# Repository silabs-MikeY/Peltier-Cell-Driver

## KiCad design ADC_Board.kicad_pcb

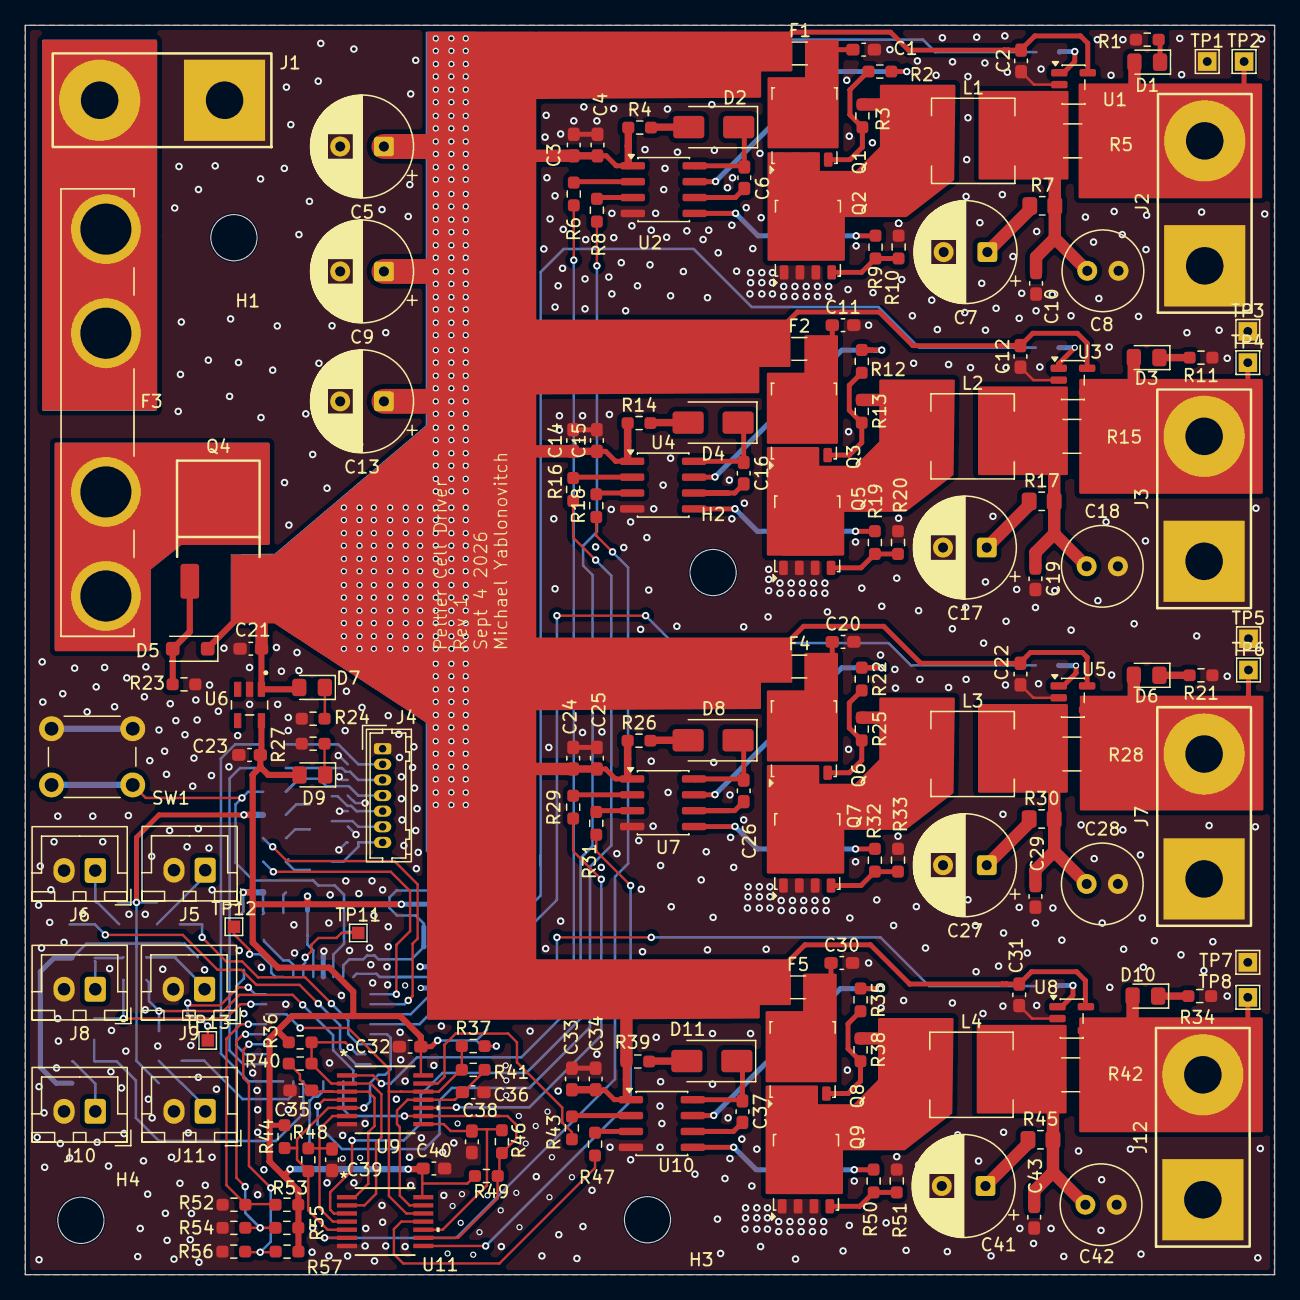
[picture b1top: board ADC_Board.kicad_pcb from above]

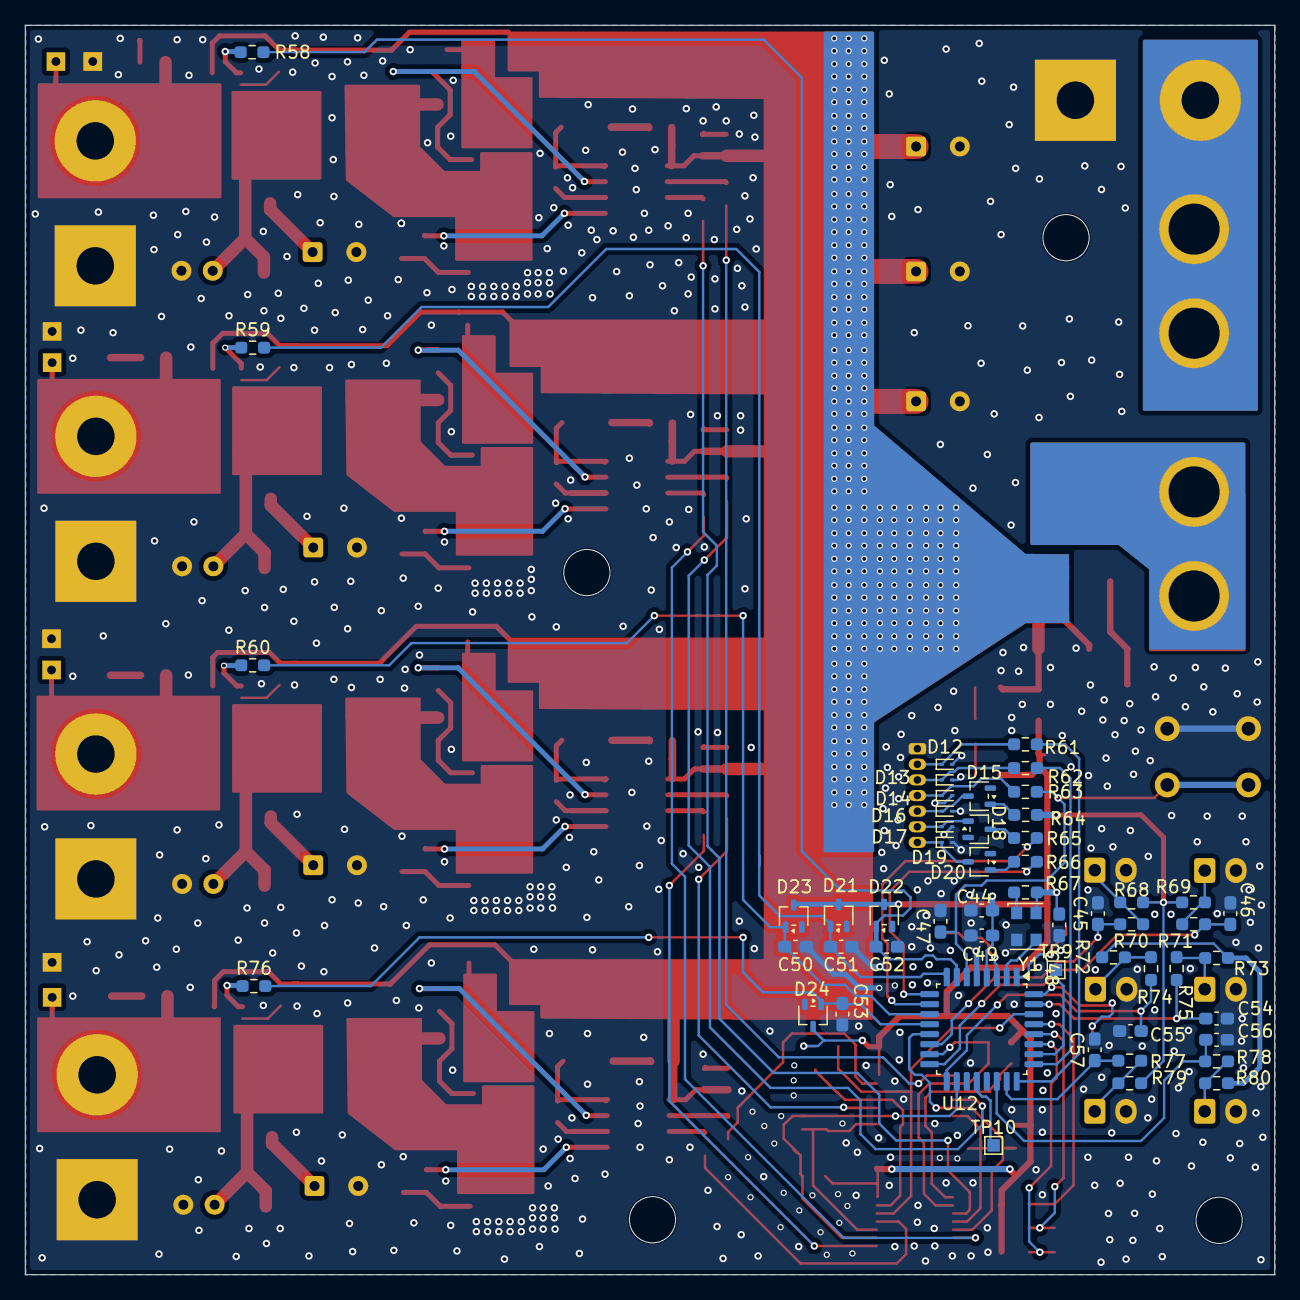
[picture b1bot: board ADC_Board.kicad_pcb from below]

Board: 4 copper layers, 100.0 x 100.0 mm, 222 parts (54 on the bottom side), 128 nets.

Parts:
C1, C11, C20, C21, C30, C45, C46, C54, C55, C56, C57: 1u; C_0603_1608Metric_Pad1.08x0.95mm_HandSolder
C2, C4, C6, C12, C15, C16, C22, C25, C26, C31, C32, C34, C37, C40, C47, C48, C49, C50, C51, C52, C53: 100n; C_0603_1608Metric_Pad1.08x0.95mm_HandSolder
C3, C14, C24, C33, C44: 4u7; C_0603_1608Metric_Pad1.08x0.95mm_HandSolder
C5, C7, C9, C13, C17, C27, C41: 100u; CP_Radial_D8.0mm_P3.50mm
C8, C18, C28, C42: 22u; C_Radial_D6.3mm_H7.0mm_P2.50mm
C10, C19, C29, C43: DNP; C_0603_1608Metric_Pad1.08x0.95mm_HandSolder
C23: 2u2; C_0603_1608Metric_Pad1.08x0.95mm_HandSolder
C35, C36, C38, C39: 330p; C_0603_1608Metric_Pad1.08x0.95mm_HandSolder
D1, D3, D6, D7, D9, D10: LED; LED_0805_2012Metric_Pad1.15x1.40mm_HandSolder
D2, D4, D8, D11: SS14; D_SMA
D5: BZT52C10; D_SOD-123F
D12, D13, D14, D16, D17, D19: ESD9B3.3ST5G; D_SOD-923
D15, D18, D20, D21, D22, D23, D24: BAT54W; SOT-323_SC-70
F1, F2, F4, F5: 5A; Fuse_1206_3216Metric
F3: 3555-2; FUSE_3555-2
H1, H2, H3, H4: MountingHole; MountingHole_3.7mm
J1, J2, J3, J7, J12: Wire_Solder_2Pin; Wire_Solder_2Pin_12-14AWG_P10mm_D3.0mm
J4: Conn_01x07_Socket; Hirose_DF13-07P-1.25DSA_1x07_P1.25mm_Vertical
J5, J6, J8, J9, J10, J11: Conn_01x02_Pin; JST_XH_B2B-XH-A_1x02_P2.50mm_Vertical
L1, L2, L3, L4: 1u; L_Changjiang_FXL0630
Q1, Q2, Q3, Q5, Q6, Q7, Q8, Q9: NVMFS5C468NL-HXY
Q4: DOD40P03; DOD40P03_TO-252_Q_PMOS_DGS
R1, R3, R10, R11, R13, R20, R21, R23, R24, R25, R27, R33, R34, R36, R37, R38, R44, R49, R51, R68, R69, R72, R73, R79, R80: 10k; R_0603_1608Metric_Pad0.98x0.95mm_HandSolder
R2, R9, R12, R19, R22, R32, R35, R50: 4r7; R_0603_1608Metric_Pad0.98x0.95mm_HandSolder
R4, R14, R26, R39: 10r; R_0603_1608Metric_Pad0.98x0.95mm_HandSolder
R5, R15, R28, R42: 5m; R_1210_3225Metric_Pad1.30x2.65mm_HandSolder
R6, R8, R16, R18, R29, R31, R43, R47, R61, R62, R63, R64, R65, R66: 100r; R_0603_1608Metric_Pad0.98x0.95mm_HandSolder
R7, R17, R30, R45: 500m; R_0805_2012Metric_Pad1.20x1.40mm_HandSolder
R40, R41, R46, R48, R58, R59, R60, R67, R70, R71, R74, R75, R76, R77, R78: 1k; R_0603_1608Metric_Pad0.98x0.95mm_HandSolder
R52, R53, R54, R55, R56, R57: DNP; R_0603_1608Metric_Pad0.98x0.95mm_HandSolder
SW1: SW_Push; SW_PUSH_6mm
TP1, TP3, TP5, TP7: GND; TestPoint_THTPad_1.5x1.5mm_Drill0.7mm
TP2, TP4, TP6, TP8: TestPoint; TestPoint_THTPad_1.5x1.5mm_Drill0.7mm
TP9, TP10, TP11, TP12, TP13: TestPoint; TestPoint_Pad_1.0x1.0mm
U1, U3, U5, U8: INA281A3; SOT-23-5
U2, U4, U7, U10: LM5109BMA; SOIC-8_3.9x4.9mm_P1.27mm
U6: TPS70933DBVR; SOT95P280X145-5N
U9: SN74HCS02PWR; TSSOP14_PW_TEX-M
U11: SN74HCS08PWR; TSSOP14_PW_TEX-M
U12: STM32G030K6Tx; LQFP-32_7x7mm_P0.8mm
Y1: HSO321S 16MHZ 3.3V; Oscillator_SMD_EuroQuartz_XO32-4Pin_3.2x2.5mm

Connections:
+3.3V: C23.1, C32.1, C40.1, C44.1, C48.2, C49.1, D9.2 (A), D21.3 (K), D22.3 (K), D23.3 (K), D24.3 (K), R36.2, R37.2, R44.2, R49.2, R53.2, R55.2, R57.2, R64.1, R67.2, R68.2, R69.2, R72.2, R73.2, R79.2, R80.2, U6.5 (OUT), U9.14 (VCC), U11.14 (VCC), U12.4 (VDD), Y1.4 (VDD)
+12V: C2.2, C3.1, C4.1, C5.1, C9.1, C12.2, C13.1, C14.1, C15.1, C21.1, C22.2, C24.1, C25.1, C31.2, C33.1, C34.1, D5.1 (K), D7.2 (A), F1.1, F2.1, F4.1, F5.1, Q4.3 (S), R4.1, R14.1, R26.1, R39.1, U1.5 (V+), U2.1 (VDD), U3.5 (V+), U4.1 (VDD), U5.5 (V+), U6.1 (IN), U7.1 (VDD), U8.5 (V+), U10.1 (VDD)
/PWM Driver/PWM3_DLY: C38.1, R46.2, U9.8 (3A), U11.10 (3B)
/PWM Driver/PWM4_DLY: C36.1, R41.2, U9.11 (4A), U11.13 (4B)
/PWM Driver/PWM_1_DLY: C35.1, R40.2, U9.3 (1B), U11.1 (1A)
/PWM Driver/PWM_2_DLY: C39.1, R48.2, U9.6 (2B), U11.4 (2A)
/Root/ADDR_0: R56.2, R57.1, U12.27 (PB3)
/Root/ADDR_1: R54.2, R55.1, U12.28 (PB4)
/Root/ADDR_2: R52.2, R53.1, U12.29 (PB5)
ADC_MOTOR_CURRENT_1: C52.2, D22.1 (A), R58.2, U12.7 (PA0)
ADC_MOTOR_CURRENT_2: C51.2, D21.1 (A), R59.2, U12.8 (PA1)
ADC_MOTOR_CURRENT_3: C50.2, D23.1 (A), R60.2, U12.11 (PA4)
ADC_MOTOR_CURRENT_4: C53.2, D24.1 (A), R76.2, U12.12 (PA5)
ADC_THERMISTOR_1: C45.1, R70.2, U12.14 (PA7)
ADC_THERMISTOR_2: C46.1, R71.2, U12.16 (PB1)
ADC_THERMISTOR_3: C55.1, R74.2, U12.17 (PB2)
ADC_THERMISTOR_4: C54.1, R75.2, U12.31 (PB7)
ADC_THERMISTOR_5: C56.1, R78.2, U12.22 (PA9/PA11)
ADC_THERMISTOR_6: C57.1, R77.2, U12.23 (PA10/PA12)
GND: C1.2, C2.1, C3.2, C4.2, C5.2, C7.2, C8.2, C9.2, C10.2, C11.2, C12.1, C13.2, C14.2, C15.2, C17.2, C18.2, C19.2, C20.2, C21.2, C22.1, C23.2, C24.2, C25.2, C27.2, C28.2, C29.2, C30.2, C31.1, C32.2, C33.2, C34.2, C35.2, C36.2, C38.2, C39.2, C40.2, C41.2, C42.2, C43.2, C44.2, C45.2, C46.2, C47.2, C48.1, C49.2, C50.1, C51.1, C52.1, C53.1, C54.2, C55.2, C56.2, C57.2, D12.2 (A2), D13.2 (A2), D14.2 (A2), D16.2 (A2), D17.2 (A2), D19.2 (A2), J1.1 (WIRE1), J2.1 (WIRE1), J3.1 (WIRE1), J4.1, J5.2, J6.2, J7.1 (WIRE1), J8.2, J9.2, J10.2, J11.2, J12.1 (WIRE1), Q2.3 (S), Q5.3 (S), Q7.3 (S), Q9.3 (S), R1.1, R10.1, R11.1, R20.1, R21.1, R23.1, R24.1, R27.1, R33.1, R34.1, R51.1, R52.1, R54.1, R56.1, SW1.2, TP1.1 (1_1), TP3.1 (1_1), TP5.1 (1_1), TP7.1 (1_1), U1.2 (GND), U2.4 (VSS), U3.2 (GND), U4.4 (VSS), U5.2 (GND), U6.2 (GND), U7.4 (VSS), U8.2 (GND), U9.7 (GND), U10.4 (VSS), U11.7 (GND), U12.5 (VSS), Y1.2 (GND)
unnamed: C7.1, R7.1
unnamed: C17.1, R17.1
unnamed: C27.1, R30.1
unnamed: C41.1, R45.1
unnamed: D1.2 (A), J2.2 (WIRE2), R5.2, TP2.1 (1_1), U1.4 (Vin-)
unnamed: D1.1 (K), R1.2
unnamed: D2.2 (A), R4.2
unnamed: C6.1, D2.1 (K), U2.8 (HB)
unnamed: D3.2 (A), J3.2 (WIRE2), R15.2, TP4.1 (1_1), U3.4 (Vin-)
unnamed: D3.1 (K), R11.2
unnamed: D4.2 (A), R14.2
unnamed: C16.1, D4.1 (K), U4.8 (HB)
unnamed: D5.2 (A), Q4.2 (G), R23.2
unnamed: D6.2 (A), J7.2 (WIRE2), R28.2, TP6.1 (1_1), U5.4 (Vin-)
unnamed: D6.1 (K), R21.2
unnamed: D7.1 (K), R24.2
unnamed: D8.2 (A), R26.2
unnamed: C26.1, D8.1 (K), U7.8 (HB)
unnamed: D9.1 (K), R27.2
unnamed: D10.2 (A), J12.2 (WIRE2), R42.2, TP8.1 (1_1), U8.4 (Vin-)
unnamed: D10.1 (K), R34.2
unnamed: D11.2 (A), R39.2
unnamed: C37.1, D11.1 (K), U10.8 (HB)
unnamed: D12.1 (A1), J4.2, R61.2
unnamed: D13.1 (A1), J4.3, R62.2
unnamed: D14.1 (A1), J4.4, R63.2
unnamed: D15.1 (A), R64.2
unnamed: D15.3 (K), D16.1 (A1), J4.5
unnamed: D17.1 (A1), D18.1 (A), J4.6
unnamed: D18.3 (K), R65.2
unnamed: D19.1 (A1), D20.3 (K), J4.7
unnamed: D20.1 (A), R66.2
unnamed: F3.1_1, F3.1_2, J1.2 (WIRE2)
unnamed: J5.1, R68.1, R70.1
unnamed: J6.1, R69.1, R71.1
unnamed: J8.1, R73.1, R75.1
unnamed: J9.1, R72.1, R74.1
unnamed: J10.1, R78.1, R80.1
unnamed: J11.1, R77.1, R79.1
unnamed: C1.1, F1.2, Q1.1 (D)
unnamed: Q1.2 (G), R2.2, R3.2
unnamed: L1.1, Q1.3 (S), Q2.1 (D), R3.1
unnamed: Q2.2 (G), R9.2, R10.2
unnamed: C11.1, F2.2, Q3.1 (D)
unnamed: Q3.2 (G), R12.2, R13.2
unnamed: L2.1, Q3.3 (S), Q5.1 (D), R13.1
unnamed: F3.2_1, F3.2_2, Q4.1 (D)
unnamed: Q5.2 (G), R19.2, R20.2
unnamed: C20.1, F4.2, Q6.1 (D)
unnamed: Q6.2 (G), R22.2, R25.2
unnamed: L3.1, Q6.3 (S), Q7.1 (D), R25.1
unnamed: Q7.2 (G), R32.2, R33.2
unnamed: C30.1, F5.2, Q8.1 (D)
unnamed: Q8.2 (G), R35.2, R38.2
unnamed: L4.1, Q8.3 (S), Q9.1 (D), R38.1
unnamed: Q9.2 (G), R50.2, R51.2
unnamed: R58.1, U1.1 (OUT)
unnamed: C8.1, C10.1, L1.2, R5.1, R7.2, U1.3 (Vin+)
unnamed: R6.2, U2.2 (HI)
unnamed: R2.1, U2.7 (HO)
unnamed: C6.2, U2.6 (HS)
unnamed: R8.2, U2.3 (LI)
unnamed: R9.1, U2.5 (LO)
unnamed: R59.1, U3.1 (OUT)
unnamed: C18.1, C19.1, L2.2, R15.1, R17.2, U3.3 (Vin+)
unnamed: R16.2, U4.2 (HI)
unnamed: R12.1, U4.7 (HO)
unnamed: C16.2, U4.6 (HS)
unnamed: R18.2, U4.3 (LI)
unnamed: R19.1, U4.5 (LO)
unnamed: R60.1, U5.1 (OUT)
unnamed: C28.1, C29.1, L3.2, R28.1, R30.2, U5.3 (Vin+)
unnamed: R29.2, U7.2 (HI)
unnamed: R22.1, U7.7 (HO)
unnamed: C26.2, U7.6 (HS)
unnamed: R31.2, U7.3 (LI)
unnamed: R32.1, U7.5 (LO)
unnamed: R76.1, U8.1 (OUT)
unnamed: C42.1, C43.1, L4.2, R42.1, R45.2, U8.3 (Vin+)
unnamed: R43.2, U10.2 (HI)
unnamed: R35.1, U10.7 (HO)
unnamed: C37.2, U10.6 (HS)
unnamed: R47.2, U10.3 (LI)
unnamed: R50.1, U10.5 (LO)
unnamed: TP9.1 (1_1), U12.26 (PA15)
unnamed: TP13.1 (1_1), U12.32 (PB8)
unnamed: TP12.1 (1_1), U12.1 (PB9)
unnamed: TP10.1 (1_1), U12.20 (PC6)
unnamed: U12.2 (PC14), Y1.3 (OUT)
unnamed: TP11.1 (1_1), U12.3 (PC15)
unnamed: R67.1, Y1.1 (Tri-State)
PWM_1: R36.1, R40.1, U9.2 (1A), U11.2 (1B), U12.15 (PB0)
PWM_1_HIGH: R6.1, U9.1 (1Y)
PWM_1_LOW: R8.1, U11.3 (1Y)
PWM_2: R44.1, R48.1, U9.5 (2A), U11.5 (2B), U12.13 (PA6)
PWM_2_HIGH: R16.1, U9.4 (2Y)
PWM_2_LOW: R18.1, U11.6 (2Y)
PWM_3: R46.1, R49.1, U9.9 (3B), U11.9 (3A), U12.18 (PA8)
PWM_3_HIGH: R29.1, U9.10 (3Y)
PWM_3_LOW: R31.1, U11.8 (3Y)
PWM_4: R37.1, R41.1, U9.12 (4B), U11.12 (4A), U12.30 (PB6)
PWM_4_HIGH: R43.1, U9.13 (4Y)
PWM_4_LOW: R47.1, U11.11 (4Y)
RESET: C47.1, R63.1, SW1.1, U12.6 (NRST)
SWCLK: R62.1, U12.25 (PA14)
SWDIO: R61.1, U12.24 (PA13)
UART_RX: R65.1, U12.10 (PA3)
UART_TX: R66.1, U12.9 (PA2)

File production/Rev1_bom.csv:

Designator,Footprint,Quantity,Value,LCSC Part #
"C1, C11, C20, C21, C30, C45, C46, C54, C55, C56, C57",0603,11,1u,C5254686
"C12, C15, C16, C2, C22, C25, C26, C31, C32, C34, C37, C4, C40, C47, C48, C49, C50, C51, C52, C53, C6",0603,21,100n,C14663
"C13, C17, C27, C41, C5, C7, C9",CP_Radial_D8.0mm_P3.50mm,7,100u,C171434
"C14, C24, C3, C33, C44",0603,5,4u7,C22399629
"C18, C28, C42, C8",C_Radial_D6.3mm_H7.0mm_P2.50mm,4,22u,C2691855
C23,0603,1,2u2,C48579298
"C35, C36, C38, C39",0603,4,330p,C22399617
"D1, D10, D3, D6, D7, D9",0805,6,LED,C110099
"D11, D2, D4, D8",D_SMA,4,SS14,C49861244
"D12, D13, D14, D16, D17, D19",D_SOD-923,6,ESD9B3.3ST5G,C96512
"D15, D18, D20, D21, D22, D23, D24",SOT-323_SC-70,7,BAT54W,C77328
D5,D_SOD-123F,1,BZT52C10,C571378
"F1, F2, F4, F5",1206,4,5A,C553924
F3,FUSE_3555-2,1,3555-2,C3203939
"J10, J11, J5, J6, J8, J9",JST_XH_B2B-XH-A_1x02_P2.50mm_Vertical,6,Conn_01x02_Pin,
J4,Hirose_DF13-07P-1.25DSA_1x07_P1.25mm_Vertical,1,Conn_01x07_Socket,C17565513
"L1, L2, L3, L4",L_Changjiang_FXL0630,4,1u,C167216
"Q1, Q2, Q3, Q5, Q6, Q7, Q8, Q9",NVMFS5C468NL-HXY,8,NVMFS5C468NL-HXY,C22366807
Q4,DOD40P03_TO-252_Q_PMOS_DGS,1,DOD40P03,C36499177
"R1, R10, R11, R13, R20, R21, R23, R24, R25, R27, R3, R33, R34, R36, R37, R38, R44, R49, R51, R68, R69, R72, R73, R79, R80",0603,25,10k,C98220
"R12, R19, R2, R22, R32, R35, R50, R9",0603,8,4r7,C137705
"R14, R26, R39, R4",0603,4,10r,C109318
"R15, R28, R42, R5",1210,4,5m,C7419996
"R16, R18, R29, R31, R43, R47, R6, R61, R62, R63, R64, R65, R66, R8",0603,14,100r,C105588
"R17, R30, R45, R7",0805,4,500m,C327217
"R40, R41, R46, R48, R58, R59, R60, R67, R70, R71, R74, R75, R76, R77, R78",0603,15,1k,C22548
SW1,SW_PUSH_6mm,1,SW_Push,C318884
"TP10, TP11, TP12, TP13, TP9",TestPoint_Pad_1.0x1.0mm,5,TestPoint,
"U1, U3, U5, U8",SOT-23-5,4,INA281A3,C1517407
"U10, U2, U4, U7",SOIC-8_3.9x4.9mm_P1.27mm,4,LM5109BMA,C116862
U11,TSSOP14_PW_TEX-M,1,SN74HCS08PWR,C2868022
U12,LQFP-32_7x7mm_P0.8mm,1,STM32G030K6Tx,C529331
U6,SOT95P280X145-5N,1,TPS70933DBVR,C89347
U9,TSSOP14_PW_TEX-M,1,SN74HCS02PWR,C2868020
Y1,Oscillator_SMD_EuroQuartz_XO32-4Pin_3.2x2.5mm,1,HSO321S 16MHZ 3.3V,C160456
